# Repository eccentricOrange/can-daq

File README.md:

# CAN-DAQ based on the ESP32-S3 Microcontroller
This project is meant to help visualize messages on a CAN bus, with an affordable and open-source solution. We provide the design and firmware files for an affordable hardware solution (we were able to manufacture it for less than INR 2000).

Key features:
-   Support for CAN 2.0 up to **1 Mbps**.
-   Support for both standard and extended CAN frames.
-   Works with a maximum **sampling rate of 1 kHz**, which is sufficient for many applications.
-   USB interface for easy connection to a computer.
-   Accepts a standardized **CAN database file (DBC)** to interpret the messages on the CAN bus.
-   Real-time plotting of CAN messages.
-   Logging to an SQLite database for later analysis, with the ability to export to CSV.

## Usage
Please see the README files in each folder of this repository for detailed instructions on how to use the hardware and software.

Please see the [manual](docs/manual/manual.md) for further guidance.

## Overall architecture

Our hardware uses an [ESP32-S3](https://www.espressif.com/en/products/socs/esp32-s3) microcontroller and an [MCP2561](https://www.microchip.com/en-us/product/mcp2561) CAN transceiver to communicate with the CAN bus. We use the on-board USB-to-UART converter to communicate with the computer.

The firmware is written in C++ using the [ESP-IDF](https://www.espressif.com/en/products/sdks/esp-idf) framework, and is provided as open-source [software in this repository](can-daq-idf/).

The GUI software is written in Python using the [Tkinter](https://docs.python.org/3/library/tkinter.html) library and [matplotlib](https://matplotlib.org/) for plotting. We use [cantools](https://github.com/cantools/cantools/tree/master) to parse the CAN messages. The GUI software is also provided as open-source [software in this repository](can-daq-pc/).

It is expected that the user provides the [CAN database file (DBC)](https://www.csselectronics.com/pages/can-dbc-file-database-intro) to tell our software how to interpret the messages on the CAN bus.

# Design considerations

## ESP32 Microcontroller
We chose to use an ESP32-S3 microcontroller for the following reasons:
-   It is a current model and is not EOL (unlike the more popular ESP32-WROOM32).
-   It has a USB-OTG port, which allows for future upgrades, including the possibility of getting higher data rates.
-   The availability of Wi-Fi and Bluetooth allows for the possibility of re-building this as a wireless device.

### Evaluating other options
-   A development board is being used to accelerate prototyping and ensure reliability, instead of soldering the microcontroller module directly onto a PCB.
-   A choice needs to be made between the ESP32-WROOM32 and the ESP32-S2 (or ESP32-S3). S2 and S3 are newer and have more features and are not EOL.
-   Up till WROOM32, the "CAN" protocol is indeed called "CAN" in the datasheet. However, for S2 and S3, it is called "TWAI" (Two-Wire Automotive Interface). Reasons seem to be legal mostly \[[source](https://github.com/espressif/esp-idf/issues/5580)\], however it is possible for Espresiff to **change specifications** in the future since TWAI is not a standard name.
-   All three boards have native support for something equivalent to CAN 2.0, with extended frames. None have CAN-FD support.
-   All three boards support at least 2 UARTs.

**[ESP32-S3 DevKitC 1](https://docs.espressif.com/projects/esp-idf/en/latest/esp32s3/hw-reference/esp32s3/user-guide-devkitc-1.html) was chosen.** The additional USB-OTG port allows us the possibility of upgrades later down the line.

Datasheets:
-   [ESP32-WROOM32](https://www.espressif.com/sites/default/files/documentation/esp32-wroom-32_datasheet_en.pdf)
-   [ESP32-S2](https://www.espressif.com/sites/default/files/documentation/esp32-s2_datasheet_en.pdf)
-   [ESP32-S3](https://www.espressif.com/sites/default/files/documentation/esp32-s3_datasheet_en.pdf)

## CAN Transceiver
Let us first review the status, features, and drawbacks of each transceiver we considered.

| Part | Status | Fastest CAN version | Cross-compatible footprint |
| --- | --- | --- | --- |
| MCP2551 | EOL (end of life) | CAN 2.0 classic CAN | None |
| MCP2561 | EOL (end of life) | CAN 2.0 classic CAN | with MCP2561FD |
| MCP2561FD | Active | CAN FD | with MCP2561 |

Most of our testing was done with the MCP2551, which cannot be considered for new designs. We wanted to choose the MCP2561FD, however it is often not in stock. Finally, the MCP2561 is a good compromise, as it is still in stock and can be replaced by the MCP2561FD in the future.

**MCP2561 was chosen, with the possibility of upgrading to MCP2561FD in the future.**

Datasheets:
-   [MCP2551](https://ww1.microchip.com/downloads/aemDocuments/documents/APID/ProductDocuments/DataSheets/20001667G.pdf)
-   [MCP2561](https://ww1.microchip.com/downloads/en/devicedoc/20005167c.pdf)
-   [MCP2561FD](https://ww1.microchip.com/downloads/aemDocuments/documents/OTH/ProductDocuments/DataSheets/20005284A.pdf)

Migration guide:
-   [MCP2561FD Migration Guide](https://ww1.microchip.com/downloads/en/DeviceDoc/90003101A.pdf)

### Additional considerations
-   SELECT already has tested the MCP2551 and a PCB implementation. However, it is EOL and the recommended replacement is the MCP2561FD.
-   MCP2551 has 3 modes selectable by the `Rs` pin (normal, standby, internal slope control), and the MCP2561FD has 2 modes only (normal, standby).
-   According to the "migration guide" from Microchip, the MCP2561FD is otherwise a drop-in replacement for the MCP2551.

## USB-to-UART Converter
-   A choice needs to be made between using UART0 (built-in) or UART1 (external).
-   Common choices for USB-to-UART converters: [FTDI](https://www.ftdichip.com/Products/ICs/FT232R.htm), [CP2102N](https://www.silabs.com/interface/usb-bridges/usbxpress), [CH340](https://www.wch-ic.com/products/CH340.html).
-   If the problem with UART0 is debug output, this can be turned off by pulling GPIO15 to GND during boot and setting the appropriate flags in `menuconfig` of IDF.

**Internal UART0 was chosen for now.** This to ensure we can quickly develop the device without introducing additional complications.

Datasheets:
-   [CP2102N](https://www.silabs.com/documents/public/data-sheets/cp2102n-datasheet.pdf)

## GUI framework
For real-time plotting, a fast framework like [PyQtGraph](https://www.pyqtgraph.org/) and [PyQt](https://www.riverbankcomputing.com/static/Docs/PyQt6/) is recommended. However, we chose to use [matplotlib](https://matplotlib.org/) and [Tkinter](https://docs.python.org/3/library/tkinter.html) for the GUI software. This is because it is easier to use and has a lower learning curve.

We will consider using PyQtGraph and PyQt in the future if we need to increase the sampling rate.

## Logging database
We chose to use an [SQLite](https://www.sqlite.org/) database for logging. This allows us to use the [Python standard library](https://docs.python.org/3/library/sqlite3.html) to interact with the database. Moreover, the database exists as a file, which means our users do not need to install a database server.

## Paper
This work was published in HardwareX, available at [DOI 10.1016/j.ohx.2026.e00743](https://doi.org/10.1016/j.ohx.2026.e00743).

If you use this in your work, please cite our paper:
```bibtex
@article{can_daq,
  title = {CAN-DAQ: An open-source, cost-effective data capture device and software for automotive research},
  journal = {HardwareX},
  volume = {25},
  pages = {e00743},
  year = {2026},
  issn = {2468-0672},
  doi = {https://doi.org/10.1016/j.ohx.2026.e00743},
  url = {https://www.sciencedirect.com/science/article/pii/S2468067226000039},
  author = {Anuj Verma and Chandram Millon Dutta and Aritra Ghosh and Sakshin M. Kanchibail and Sneha Harish and Rishvanth S.K. and Shaurya Chandra and Siddharth Das and Selvakumar K.},
  keywords = {Automotive, Controller Area Network (CAN), Data acquisition (DAQ), CAN database (DBC), Real-time graphing, Database management},
}
```

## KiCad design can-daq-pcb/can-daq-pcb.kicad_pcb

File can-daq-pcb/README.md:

# CAN-DAQ ESP32 PCB

This is the PCB for the ESP32 that is used in the CAN-DAQ project. Gerber files, BOM, and 3D printing files for the case are all available in the releases section on GitHub.

## Pin-out
Refer to the pin-out for [ESP32-S3 DevKitC 1](https://docs.espressif.com/projects/esp-idf/en/latest/esp32s3/hw-reference/esp32s3/user-guide-devkitc-1.html).

### Pin-out for the microcontroller

| ESP Pin | Function | Connected to |
| --- | --- | --- |
| GPIO6 | CAN Rx | MCP2651FD CAN Rx |
| GPIO7 | CAN Tx | MCP2651FD CAN Tx |
| GPIO4 | CAN Standby | MCP2651FD STBY (10k pull-down) |
| GPIO5 | Status | Status LED |
| GPIO46 | Disable debug log | Pull-up resistor (10k to 5V) |

### Pin-out for the DE9 CAN connector
| DE9 Pin | Function | Connected to |
| --- | --- | --- |
| 2 | CANL | MCP2651FD CANL |
| 7 | CANH | MCP2651FD CANH |
| 3 | CAN GND | GND |
| shield |  | GND |

## USB specification
| Property | Value |
| --- | --- |
| USB standard | USB 2.0 |
| Connector | USB micro-B |
| Maximum speed | 3 Mbit/s |

## Design decisions

### DE9 ground
The CAN ground of the DE9 connector is connected to the main ground of the circuit. In case the differential voltages are not referenced to the same ground, the CAN bus will not work properly otherwise.

Sources:
- https://electronics.stackexchange.com/a/519395/323565
- https://electronics.stackexchange.com/q/476129/323565

### ESP32 log output disable
The ESP32 has a pull-up resistor on GPIO46 to disable the debug log output. We do this to make ensure that our GUI software receives only clean data.

Source: [Section "8.3 ROM Messages Printing Control" of the ESP32-S3 Technical Reference Manual](https://www.espressif.com/sites/default/files/documentation/esp32-s3_technical_reference_manual_en.pdf)

### CAN Transceiver output enable
The MCP2651FD CAN transceiver has a STBY pin that can be used to enable or disable the transceiver. We use GPIO4 to control this pin. The STBY pin is pulled down to ground with a 10k resistor (enabled) by default.

Source: [Section "1.1 Mode Control Block" of the MCP2651FD datasheet](https://ww1.microchip.com/downloads/en/DeviceDoc/20005284A.pdf)

## Screenshots

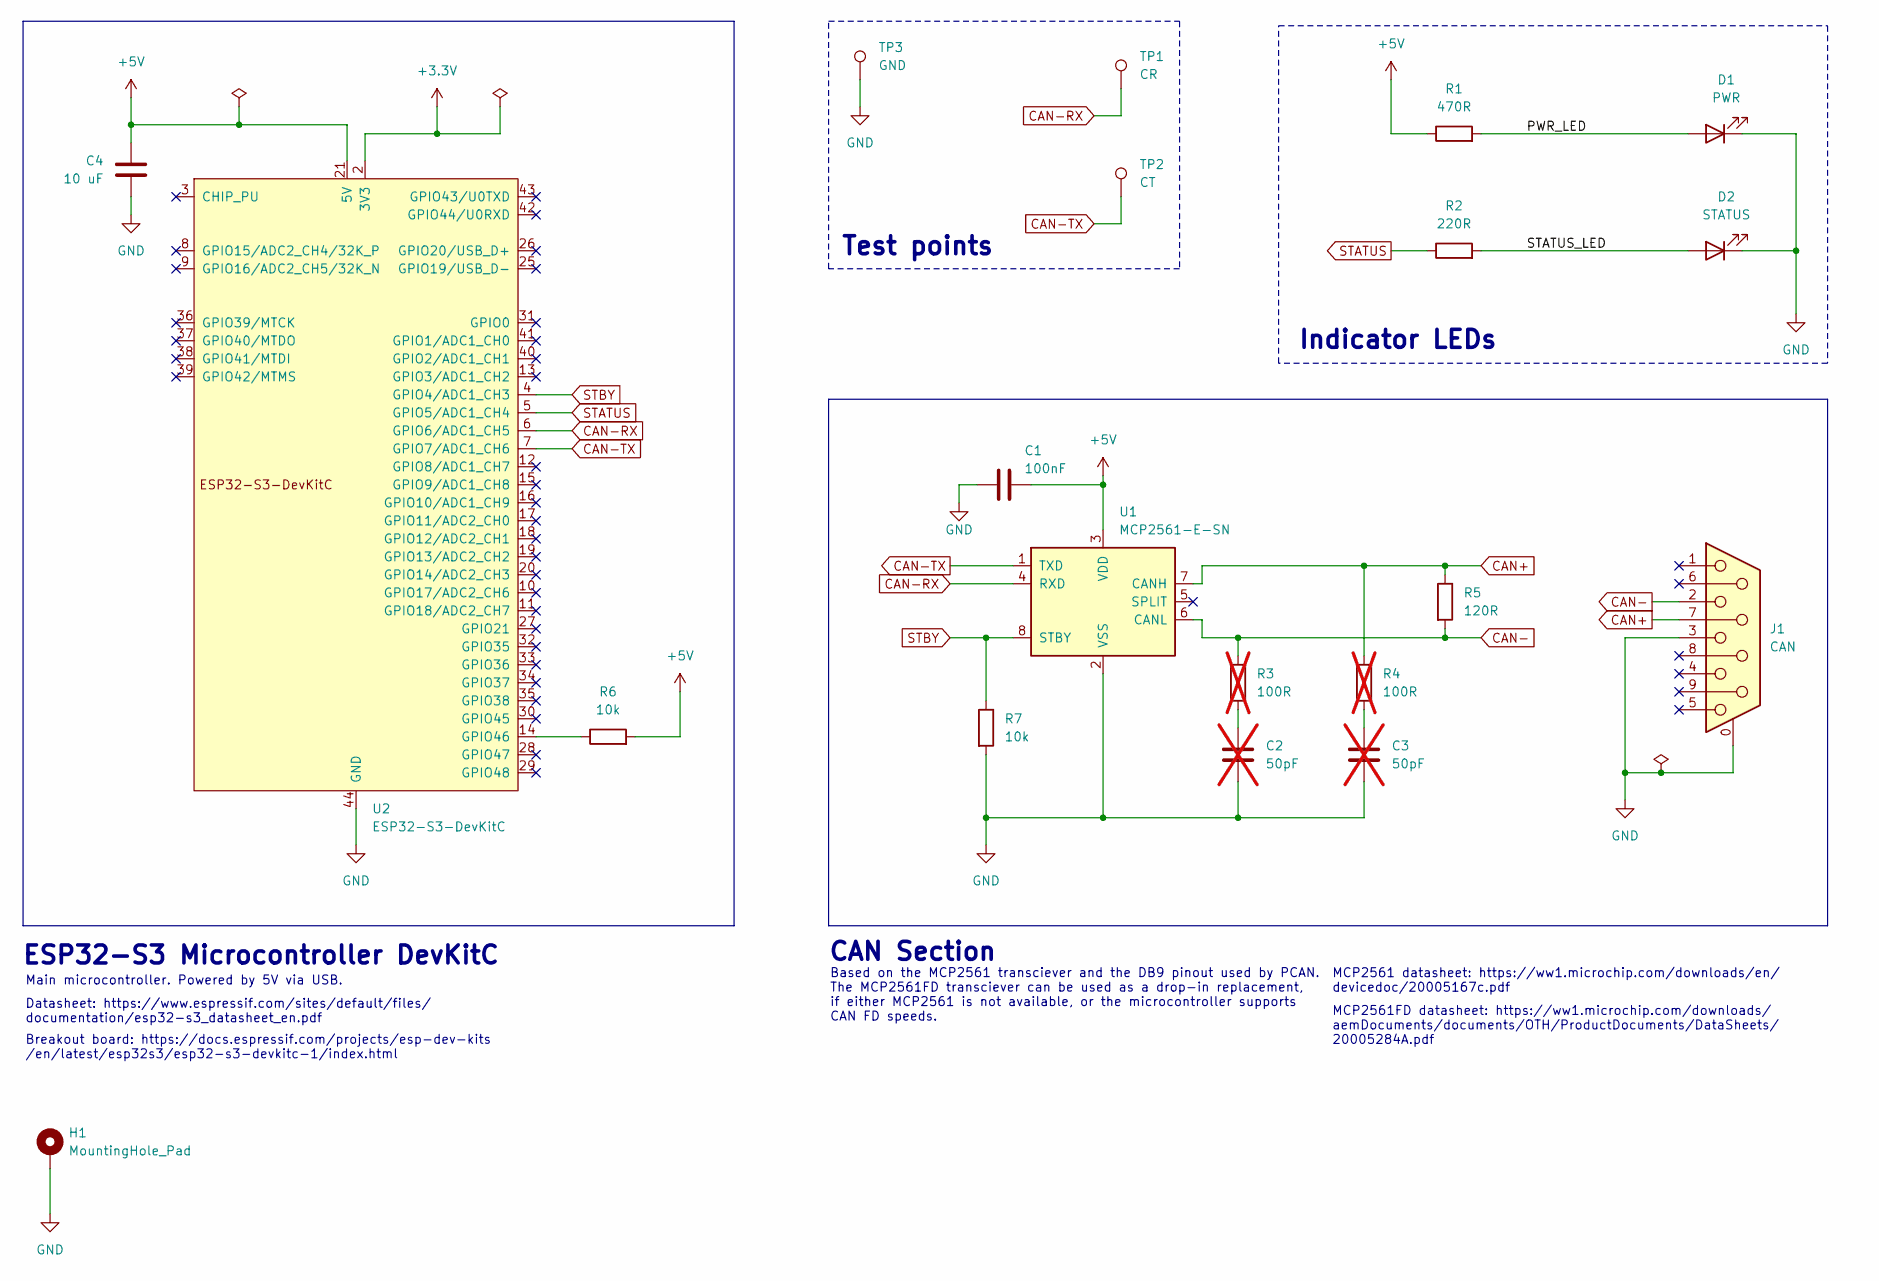
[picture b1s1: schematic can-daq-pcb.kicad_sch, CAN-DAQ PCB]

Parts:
C1: 100nF; C_0805_2012Metric_Pad1.18x1.45mm_HandSolder; MPN CC0805KRX7R9BB104; JLC C49678
C2, C3: 50pF; C_1206_3216Metric_Pad1.33x1.80mm_HandSolder; MPN FCC1206N470J102DT; JLC C5137553; not fitted
C4: 10 uF; C_1206_3216Metric_Pad1.33x1.80mm_HandSolder; MPN CL31A106KBHNNNE; JLC C13585
D1: PWR; LED_D3.0mm; MPN TZ-L2-03YYBR2RDJ30-003; JLC C779429
D2: STATUS; LED_D3.0mm; MPN TJ-L3FYTGCBMCGSFLC6B-A5; JLC C330760
H1: MountingHole_Pad; MountingHole_3.2mm_M3_Pad_Via
J1: CAN; DSUB-9_Female_Horizontal_P2.77x2.84mm_EdgePinOffset4.94mm_H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; MPN DS1037-09FNAKT74-0CC; JLC C75749
R1: 470R; R_1206_3216Metric_Pad1.30x1.75mm_HandSolder; MPN RC1206FR-07470RL; JLC C114945
R2: 220R; R_1206_3216Metric_Pad1.30x1.75mm_HandSolder; MPN 1206W4J0221T5E; JLC C25363
R3, R4: 100R; R_1206_3216Metric_Pad1.30x1.75mm_HandSolder; MPN 1206W4F1000T5E; JLC C17901; not fitted
R5: 120R; R_1206_3216Metric_Pad1.30x1.75mm_HandSolder; MPN 1206W4F1200T5E; JLC C17909
R6, R7: 10k; R_1206_3216Metric_Pad1.30x1.75mm_HandSolder; MPN 1206W4F1002T5E; JLC C17902
TP1: CR; TestPoint_THTPad_1.0x1.0mm_Drill0.5mm
TP2: CT; TestPoint_THTPad_1.0x1.0mm_Drill0.5mm
TP3: GND; TestPoint_THTPad_1.0x1.0mm_Drill0.5mm
U1: MCP2561-E-SN; SOIC-8_3.9x4.9mm_P1.27mm; MPN MCP2561-E/SN; JLC C219833
U2: ESP32-S3-DevKitC; MPN ESP32-S3-DEVKITC-1-N8; JLC C20438410

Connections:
+3.3V: U2.1 (3V3), U2.2 (3V3)
+5V: C1.1, C4.1, R1.1, R6.2, U1.3 (VDD), U2.21 (5V)
/PWR_LED: D1.2 (A), R1.2
/STATUS_LED: D2.2 (A), R2.2
CAN+: J1.7, R4.1, R5.1, U1.7 (CANH)
CAN-: J1.2, R3.1, R5.2, U1.6 (CANL)
CAN-RX: TP1.1, U1.4 (RXD), U2.6 (GPIO6/ADC1_CH5)
CAN-TX: TP2.1, U1.1 (TXD), U2.7 (GPIO7/ADC1_CH6)
GND: C1.2, C2.2, C3.2, C4.2, D1.1 (K), D2.1 (K), H1.1, J1.0 (PAD), J1.3, R7.2, TP3.1, U1.2 (VSS), U2.22 (GND), U2.23 (GND), U2.24 (GND), U2.44 (GND)
unnamed: C2.1, R3.2
unnamed: C3.1, R4.2
unnamed: R6.1, U2.14 (GPIO46)
STATUS: R2.1, U2.5 (GPIO5/ADC1_CH4)
STBY: R7.1, U1.8 (STBY), U2.4 (GPIO4/ADC1_CH3)

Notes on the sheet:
Main microcontroller. Powered by 5V via USB.
Based on the MCP2561 transciever and the DB9 pinout used by PCAN. The MCP2561FD transciever can be used as a drop-in replacement, if either MCP2561 is not available, or the microcontroller supports CAN FD speeds.
CAN Section
Indicator LEDs
Datasheet: https://www.espressif.com/sites/default/files/ documentation/esp32-s3_datasheet_en.pdf
Breakout board: https://docs.espressif.com/projects/esp-dev-kits /en/latest/esp32s3/esp32-s3-devkitc-1/index.html
MCP2561 datasheet: https://ww1.microchip.com/downloads/en/ devicedoc/20005167c.pdf
MCP2561FD datasheet: https://ww1.microchip.com/downloads/ aemDocuments/documents/OTH/ProductDocuments/DataSheets/ 20005284A.pdf
ESP32-S3 Microcontroller DevKitC
Test points

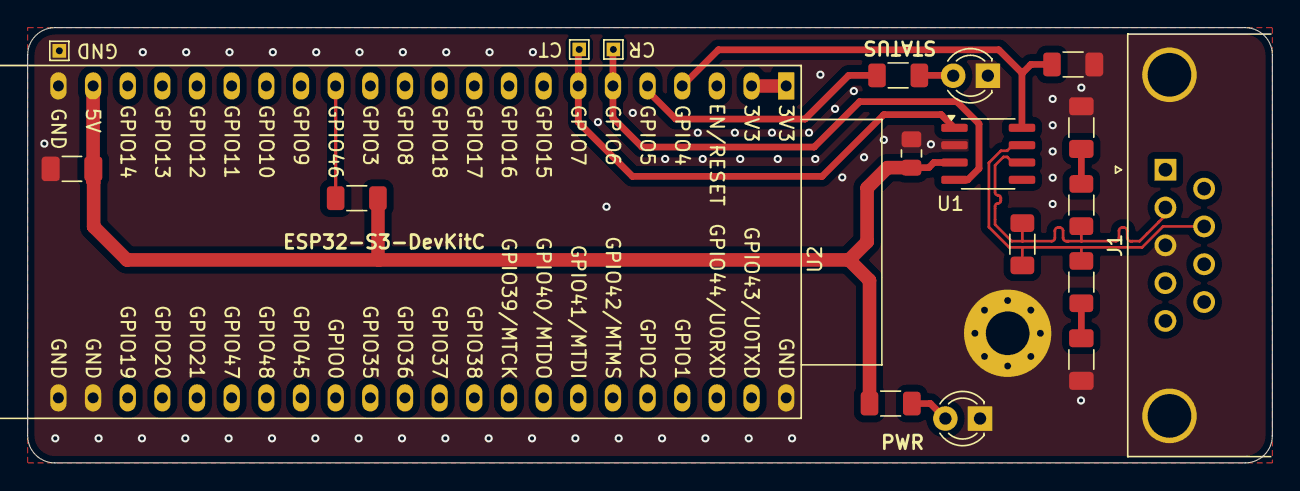
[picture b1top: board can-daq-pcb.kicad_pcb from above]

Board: 2 copper layers, 91.2 x 31.9 mm, 20 parts (0 on the bottom side), 14 nets.

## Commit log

2025-09-20 at least compiles with BotSpeak
2025-09-20 timestamp
2026-02-10 add citation detail
